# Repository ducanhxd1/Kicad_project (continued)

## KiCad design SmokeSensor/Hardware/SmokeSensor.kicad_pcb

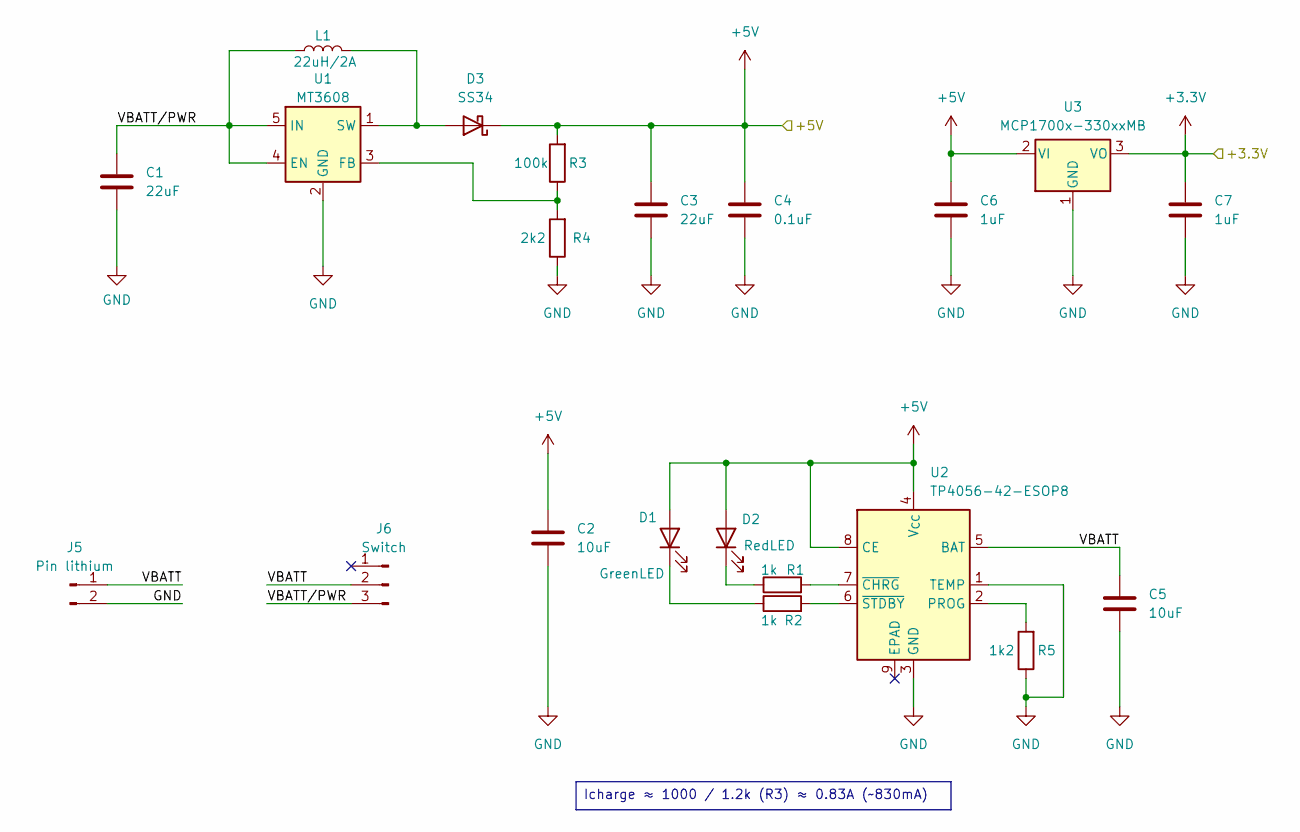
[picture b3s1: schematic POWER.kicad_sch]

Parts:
C1, C3: 22uF; C_0805_2012Metric_Pad1.18x1.45mm_HandSolder
C2, C5: 10uF; C_0805_2012Metric_Pad1.18x1.45mm_HandSolder
C4: 0.1uF; C_0805_2012Metric_Pad1.18x1.45mm_HandSolder
C6, C7: 1uF; C_0805_2012Metric_Pad1.18x1.45mm_HandSolder
D1: GreenLED; LED_0805_2012Metric_Pad1.15x1.40mm_HandSolder
D2: RedLED; LED_0805_2012Metric_Pad1.15x1.40mm_HandSolder
D3: SS34; D_SMA
J5: Pin lithium; JST_PH_S2B-PH-K_1x02_P2.00mm_Horizontal
J6: Switch; PinHeader_1x03_P2.54mm_Vertical
L1: 22uH/2A; L_10.4x10.4_H4.8
R1, R2: 1k; R_0805_2012Metric_Pad1.20x1.40mm_HandSolder
R3: 100k; R_0805_2012Metric_Pad1.20x1.40mm_HandSolder
R4: 2k2; R_0805_2012Metric_Pad1.20x1.40mm_HandSolder
R5: 1k2; R_0805_2012Metric_Pad1.20x1.40mm_HandSolder
U1: MT3608; SOT-23-6
U2: TP4056-42-ESOP8; SOIC-8-1EP_3.9x4.9mm_P1.27mm_EP2.41x3.3mm_ThermalVias
U3: MCP1700x-330xxMB; SOT-89-3

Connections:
+3.3V: C7.1, U3.3 (VO); also elsewhere on the board
+5V: C2.1, C3.1, C4.1, C6.1, D1.2 (A), D2.2 (A), D3.1 (K), R3.2, U2.4 (V_{CC}), U2.8 (CE), U3.2 (VI); also elsewhere on the board
/POWER/VBATT: C5.1, J5.1, J6.2, U2.5 (BAT)
/POWER/VBATT/PWR: C1.1, J6.3, L1.1, U1.4 (EN), U1.5 (IN)
GND: C1.2, C2.2, C3.2, C4.2, C5.2, C6.2, C7.2, J5.2, R4.1, R5.1, U1.2 (GND), U2.1 (TEMP), U2.3 (GND), U3.1 (GND); also elsewhere on the board
unnamed: D1.1 (K), R2.1
unnamed: D2.1 (K), R1.1
unnamed: D3.2 (A), L1.2, U1.1 (SW)
unnamed: R3.1, R4.2, U1.3 (FB)
unnamed: R5.2, U2.2 (PROG)
unnamed: R1.2, U2.7 (~CHRG)
unnamed: R2.2, U2.6 (~STDBY)

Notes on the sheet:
Icharge ≈ 1000 / 1.2k (R3) ≈ 0.83A (~830mA)

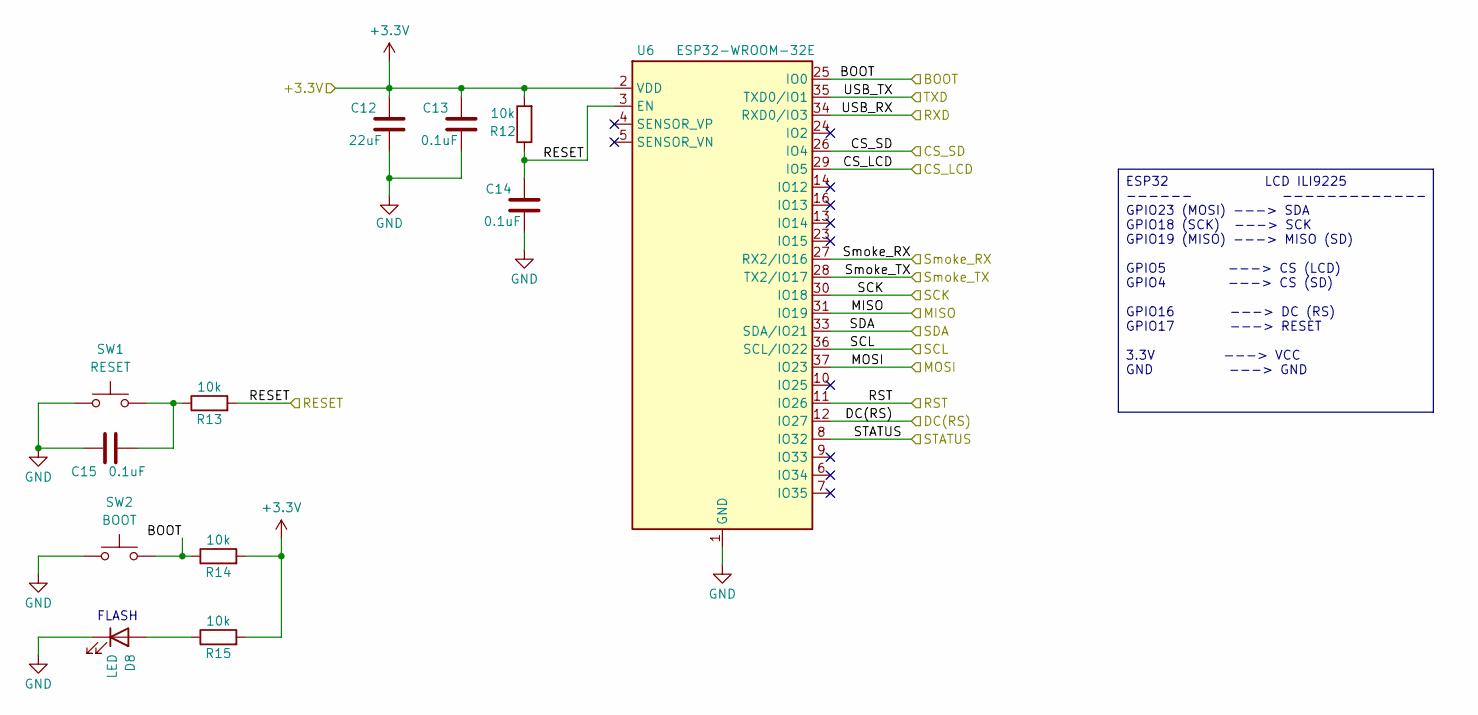
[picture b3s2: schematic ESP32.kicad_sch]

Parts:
C12: 22uF; C_0805_2012Metric_Pad1.18x1.45mm_HandSolder
C13, C14, C15: 0.1uF; C_0805_2012Metric_Pad1.18x1.45mm_HandSolder
D8: LED; LED_0805_2012Metric_Pad1.15x1.40mm_HandSolder
R12, R13, R14, R15: 10k; R_0805_2012Metric_Pad1.20x1.40mm_HandSolder
SW1: RESET; SW_Tactile_SPST_NO_Straight_CK_PTS636Sx25SMTRLFS
SW2: BOOT; SW_Tactile_SPST_NO_Straight_CK_PTS636Sx25SMTRLFS
U6: ESP32-WROOM-32E; ESP32-WROOM-32D

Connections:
+3.3V: C12.1, C13.1, R12.2, R14.2, R15.2, U6.2 (VDD); also elsewhere on the board
/ESP32/BOOT: R14.1, SW2.2, U6.25 (IO0); also elsewhere on the board
/ESP32/CS_LCD: U6.29 (IO5); also elsewhere on the board
/ESP32/CS_SD: U6.26 (IO4); also elsewhere on the board
/ESP32/DC(RS): U6.12 (IO27); also elsewhere on the board
/ESP32/MISO: U6.31 (IO19); also elsewhere on the board
/ESP32/MOSI: U6.37 (IO23); also elsewhere on the board
/ESP32/RESET: C14.1, R12.1, R13.2, U6.3 (EN); also elsewhere on the board
/ESP32/RST: U6.11 (IO26); also elsewhere on the board
/ESP32/SCK: U6.30 (IO18); also elsewhere on the board
/ESP32/SCL: U6.36 (SCL/IO22); also elsewhere on the board
/ESP32/SDA: U6.33 (SDA/IO21); also elsewhere on the board
/ESP32/STATUS: U6.8 (IO32); also elsewhere on the board
/ESP32/Smoke_RX: U6.27 (RX2/IO16); also elsewhere on the board
/ESP32/Smoke_TX: U6.28 (TX2/IO17); also elsewhere on the board
/ESP32/USB_RX: U6.34 (RXD0/IO3); also elsewhere on the board
/ESP32/USB_TX: U6.35 (TXD0/IO1); also elsewhere on the board
GND: C12.2, C13.2, C14.2, C15.1, D8.1 (K), SW1.1, SW2.1, U6.1 (GND), U6.15 (GND), U6.38 (GND), U6.39 (GND); also elsewhere on the board
unnamed: C15.2, R13.1, SW1.2
unnamed: D8.2 (A), R15.1

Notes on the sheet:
FLASH
ESP32 LCD ILI9225 ------ ------------- GPIO23 (MOSI) ---> SDA GPIO18 (SCK) ---> SCK GPIO19 (MISO) ---> MISO (SD) GPIO5 ---> CS (LCD) GPIO4 ---> CS (SD) GPIO16 ---> DC (RS) GPIO17 ---> RESET 3.3V ---> VCC GND ---> GND

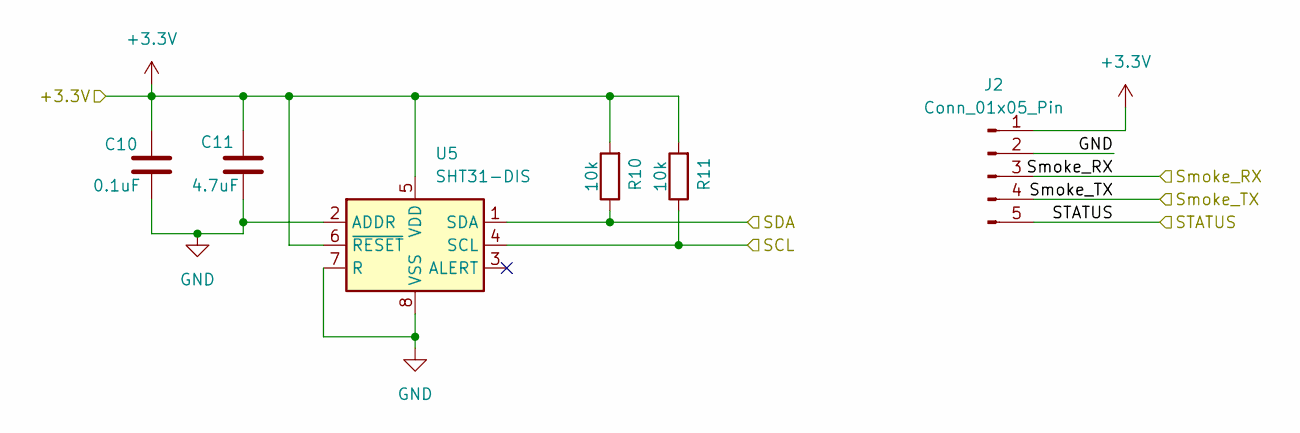
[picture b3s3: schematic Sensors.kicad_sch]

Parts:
C10: 0.1uF; C_0805_2012Metric_Pad1.18x1.45mm_HandSolder
C11: 4.7uF; C_0805_2012Metric_Pad1.18x1.45mm_HandSolder
J2: Conn_01x05_Pin; PinHeader_1x05_P2.54mm_Vertical
R10, R11: 10k; R_0805_2012Metric_Pad1.20x1.40mm_HandSolder
U5: SHT31-DIS; Sensirion_DFN-8-1EP_2.5x2.5mm_P0.5mm_EP1.1x1.7mm

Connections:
+3.3V: C10.1, C11.1, J2.1, R10.2, R11.2, U5.5 (VDD), U5.6 (~RESET); also elsewhere on the board
/ESP32/SCL: R11.1, U5.4 (SCL); also elsewhere on the board
/ESP32/SDA: R10.1, U5.1 (SDA); also elsewhere on the board
/ESP32/STATUS: J2.5; also elsewhere on the board
/ESP32/Smoke_RX: J2.4; also elsewhere on the board
/ESP32/Smoke_TX: J2.3; also elsewhere on the board
GND: C10.2, C11.2, J2.2, U5.2 (ADDR), U5.7 (R), U5.8 (VSS), U5.9 (VSS); also elsewhere on the board

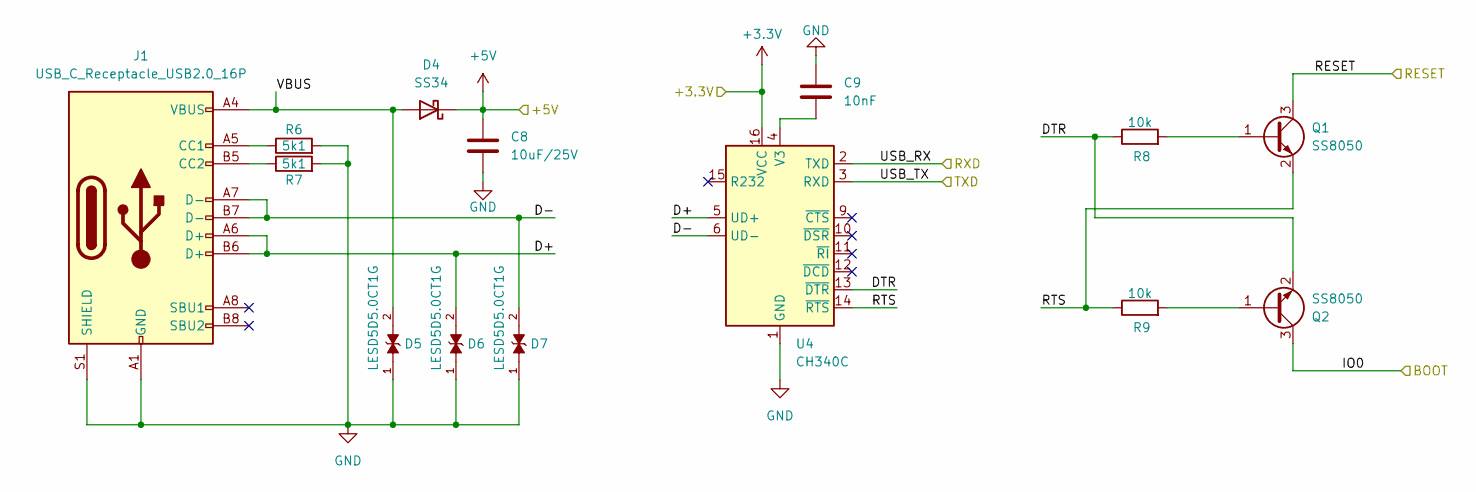
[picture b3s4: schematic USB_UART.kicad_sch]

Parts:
C8: 10uF/25V; C_0805_2012Metric_Pad1.18x1.45mm_HandSolder
C9: 10nF; C_0805_2012Metric_Pad1.18x1.45mm_HandSolder
D4: SS34; D_SMA
D5, D6, D7: LESD5D5.0CT1G; TVS_LESD5D5.0CT1G; PARTREV O
J1: USB_C_Receptacle_USB2.0_16P; USB_C_Receptacle_HCTL_HC-TYPE-C-16P-01A
Q1, Q2: SS8050; SOT-23
R6, R7: 5k1; R_0805_2012Metric_Pad1.20x1.40mm_HandSolder
R8, R9: 10k; R_0805_2012Metric_Pad1.20x1.40mm_HandSolder
U4: CH340C; SOIC-16_3.9x9.9mm_P1.27mm

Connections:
+3.3V: U4.16 (VCC); also elsewhere on the board
+5V: C8.1, D4.1 (K); also elsewhere on the board
/ESP32/BOOT: Q2.3 (C); also elsewhere on the board
/ESP32/RESET: Q1.3 (C); also elsewhere on the board
/ESP32/USB_RX: U4.3 (RXD); also elsewhere on the board
/ESP32/USB_TX: U4.2 (TXD); also elsewhere on the board
/USB UART/D+: D6.2, J1.A6 (D+), J1.B6 (D+), U4.5 (UD+)
/USB UART/D-: D7.2, J1.A7 (D-), J1.B7 (D-), U4.6 (UD-)
/USB UART/DTR: Q2.2 (E), R8.1, U4.13 (~DTR)
/USB UART/RTS: Q1.2 (E), R9.1, U4.14 (~RTS)
/USB UART/VBUS: D4.2 (A), D5.2, J1.A4 (VBUS), J1.A9 (VBUS), J1.B4 (VBUS), J1.B9 (VBUS)
GND: C8.2, C9.1, D5.1, D6.1, D7.1, J1.A1 (GND), J1.A12 (GND), J1.B1 (GND), J1.B12 (GND), J1.S1 (SHIELD), R6.2, R7.2, U4.1 (GND); also elsewhere on the board
unnamed: J1.A5 (CC1), R6.1
unnamed: J1.B5 (CC2), R7.1
unnamed: Q1.1 (B), R8.2
unnamed: Q2.1 (B), R9.2
unnamed: C9.2, U4.4 (V3)

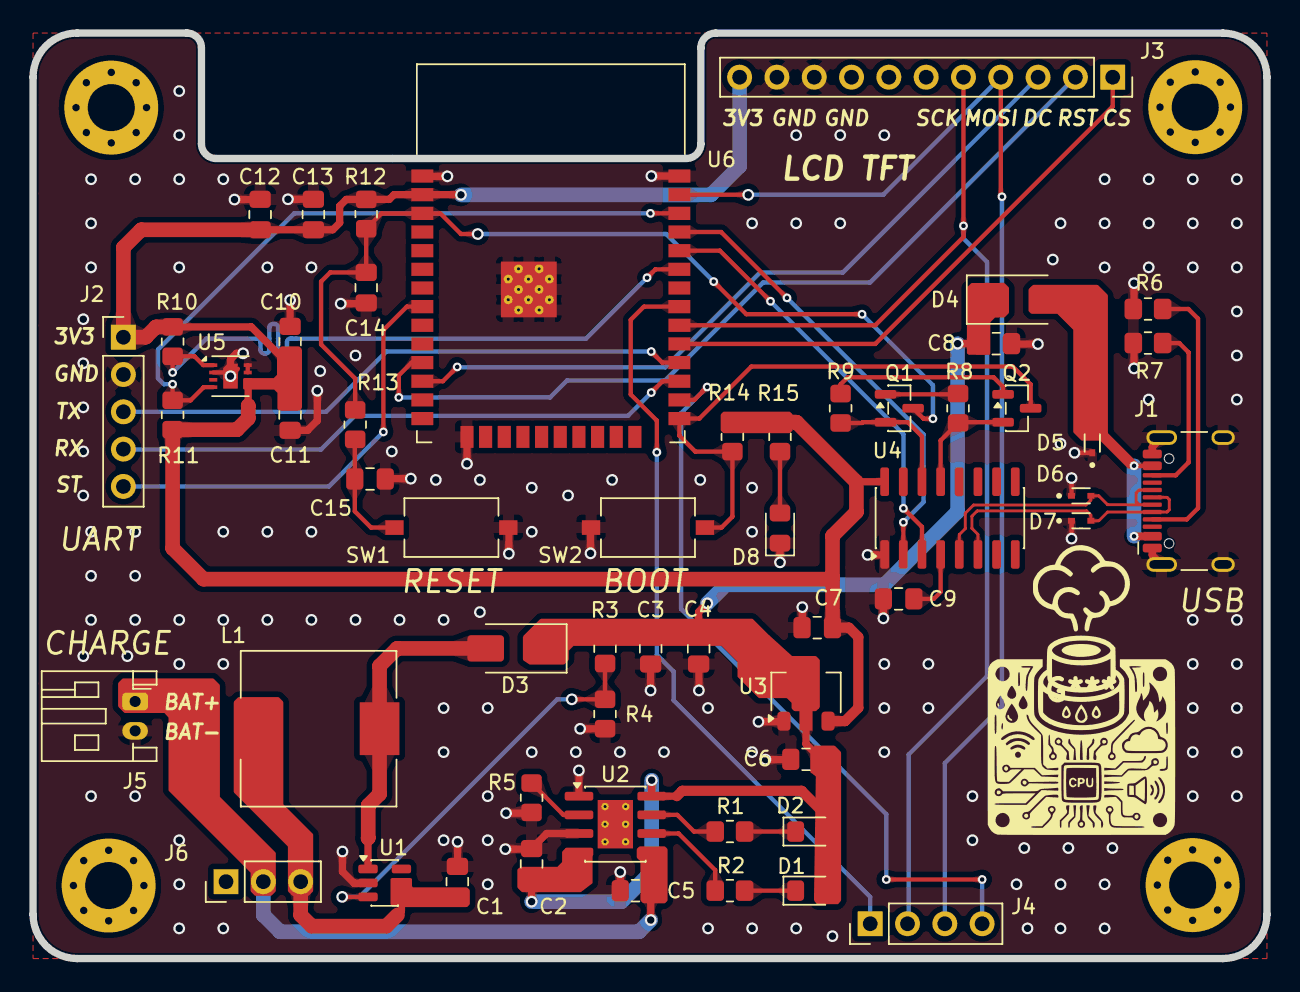
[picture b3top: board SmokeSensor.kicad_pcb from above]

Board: 2 copper layers, 84.0 x 63.0 mm, 55 parts (0 on the bottom side), 40 nets.

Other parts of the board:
J3: Conn_01x11; PinSocket_1x11_P2.54mm_Vertical
J4: Conn_01x04; PinHeader_1x04_P2.54mm_Vertical

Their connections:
+3.3V: J3.11; also elsewhere on the board
/ESP32/CS_LCD: J3.1; also elsewhere on the board
/ESP32/CS_SD: J4.4; also elsewhere on the board
/ESP32/DC(RS): J3.3; also elsewhere on the board
/ESP32/MISO: J4.1; also elsewhere on the board
/ESP32/MOSI: J3.4, J4.3; also elsewhere on the board
/ESP32/RST: J3.2; also elsewhere on the board
/ESP32/SCK: J3.5, J4.2; also elsewhere on the board
GND: J3.9, J3.10; also elsewhere on the board

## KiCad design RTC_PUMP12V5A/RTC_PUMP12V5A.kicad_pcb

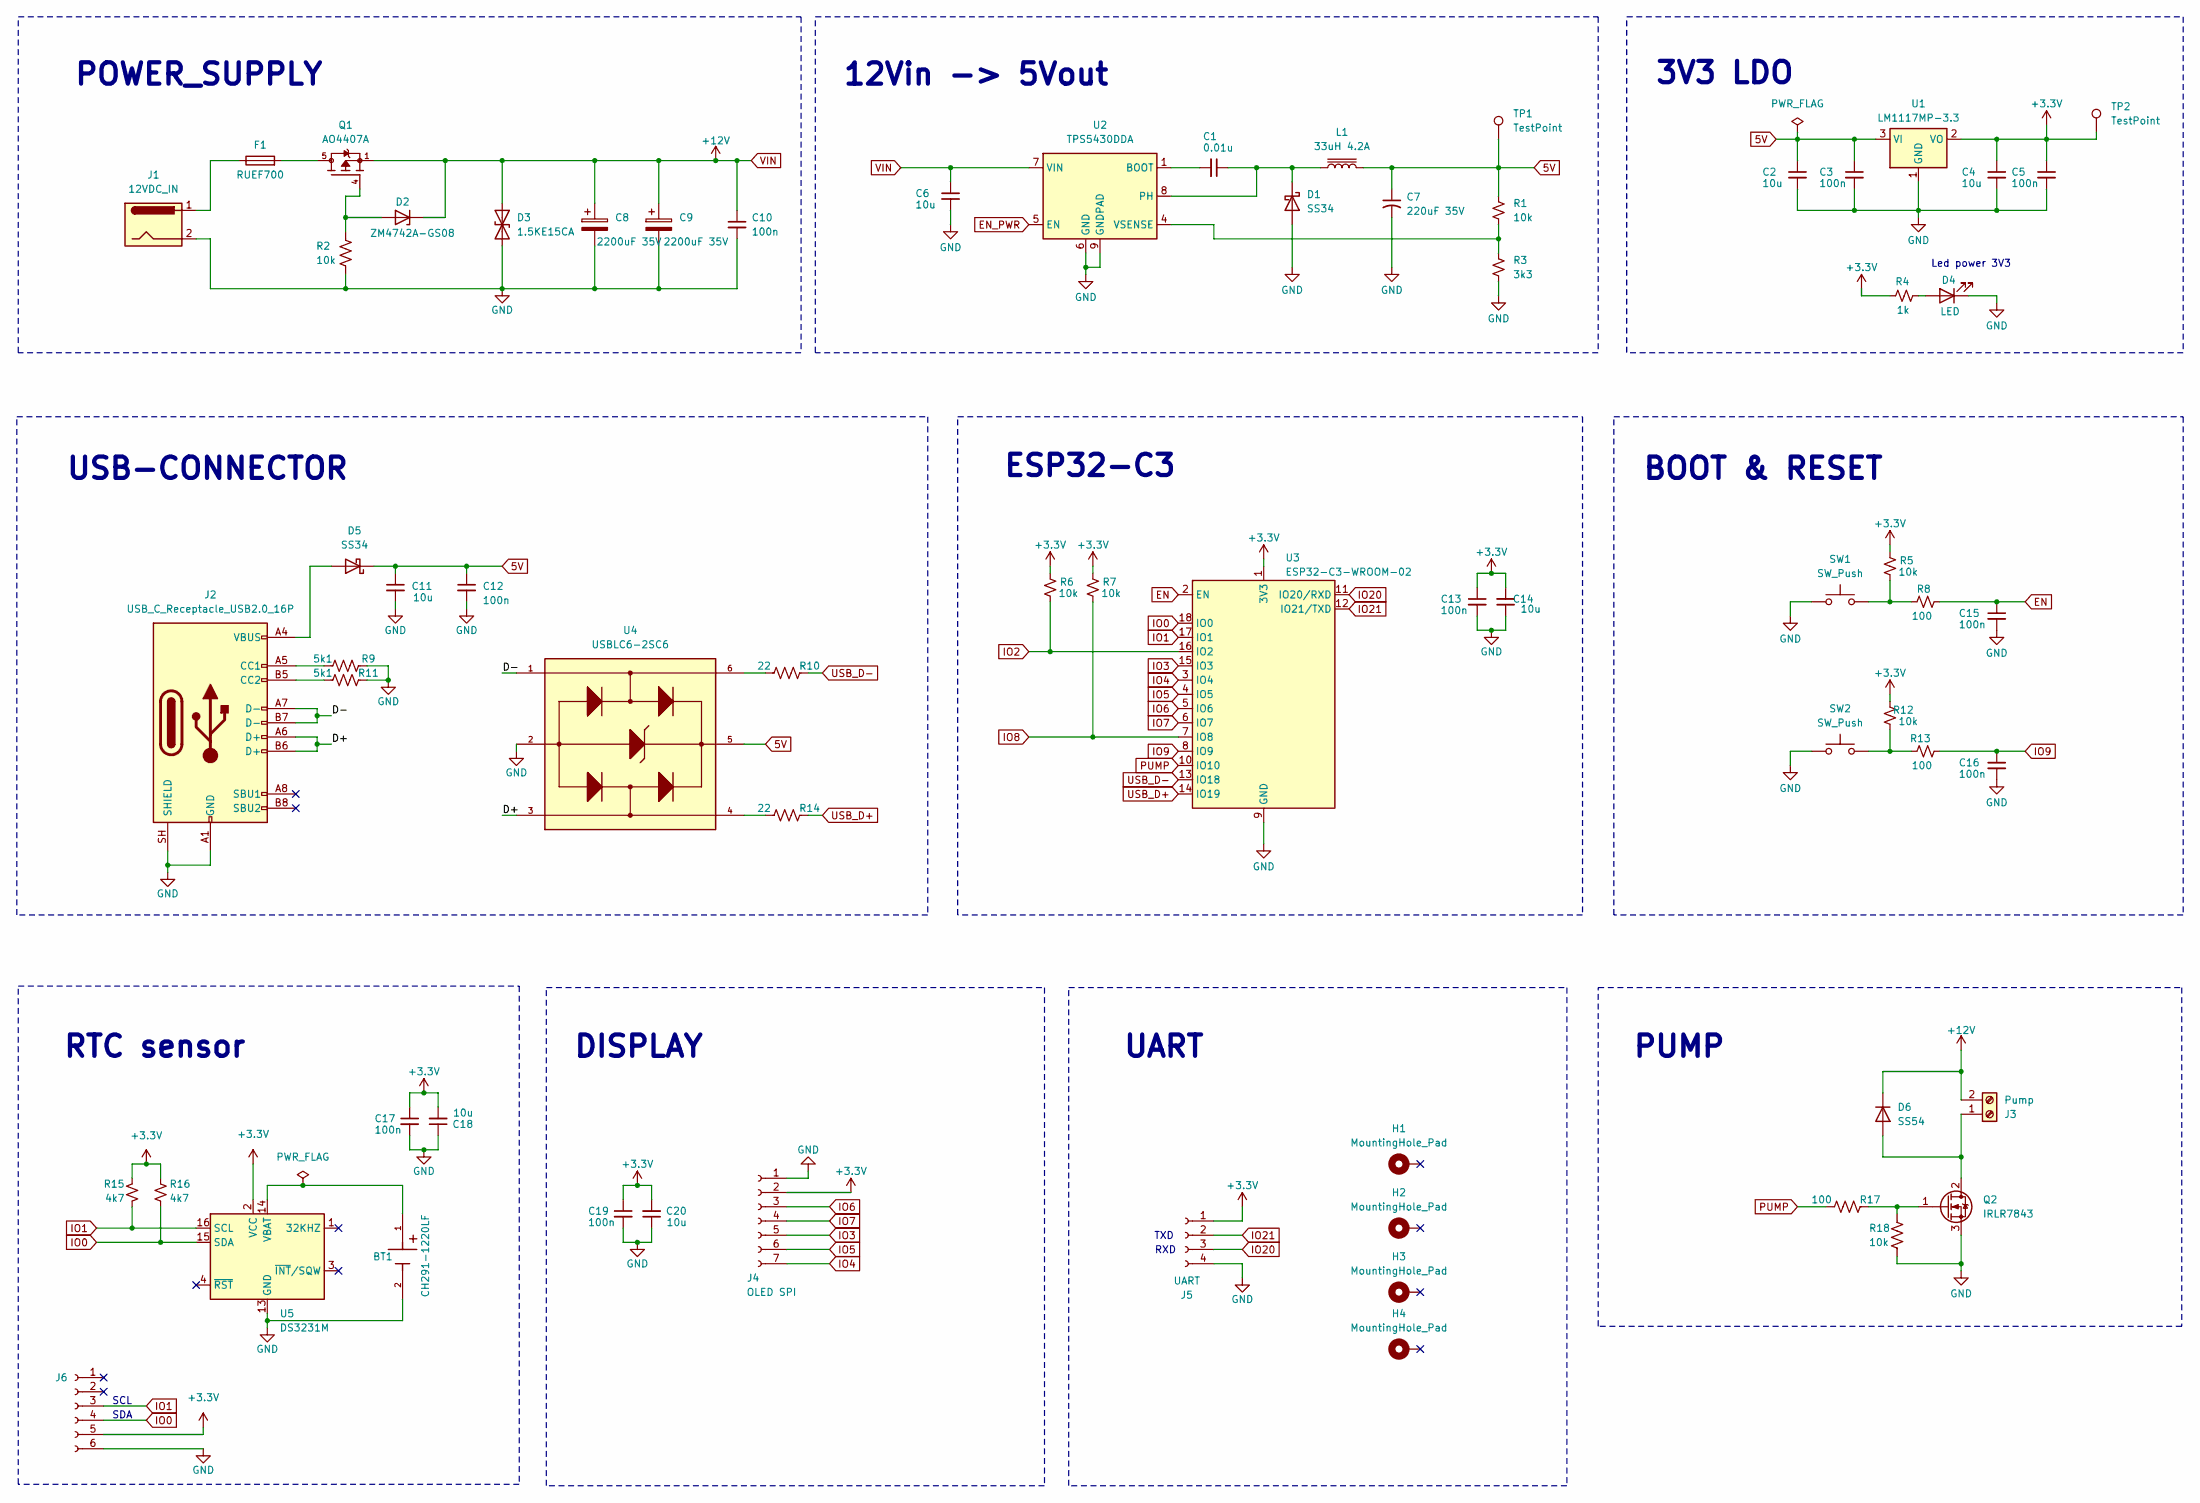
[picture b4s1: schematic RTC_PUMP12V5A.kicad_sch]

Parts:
BT1: CH291-1220LF; Battery_Panasonic_CR2032-HFN_Horizontal_CircularHoles; PARTREV A
C1: 0.01u; C_0805_2012Metric
C2, C4, C6, C11, C14, C18, C20: 10u; C_0805_2012Metric
C3, C5, C10, C12, C13, C15, C16, C17, C19: 100n; C_0805_2012Metric
C7: 220uF 35V; CP_Elec_8x10.5
C8, C9: 2200uF 35V; CP_Radial_D16.0mm_P7.50mm
D1, D5: SS34; D_SMA
D2: ZM4742A-GS08; D_MELF_Handsoldering
D3: 1.5KE15CA; D_DO-201AD_P15.24mm_Horizontal
D4: LED; LED_0805_2012Metric
D6: SS54; ST_D_SMC
F1: RUEF700; FUSRR505W81L660T250H1360
H1, H2, H3, H4: MountingHole_Pad; MountingHole_3.5mm_Pad
J1: 12VDC_IN; BarrelJack_Horizontal
J2: USB_C_Receptacle_USB2.0_16P; USB_C_Receptacle_HRO_TYPE-C-31-M-12
J3: Pump; PhoenixContact_MC_1,5_2-G-3.81_1x02_P3.81mm_Horizontal
J4: OLED SPI; PinSocket_1x07_P2.54mm_Vertical
J5: UART; JST_XH_B4B-XH-A_1x04_P2.50mm_Vertical
J6: Conn_01x06_Socket; PinSocket_1x06_P2.54mm_Vertical
L1: 33uH 4.2A; L_Bourns_SRR1208_12.7x12.7mm
Q1: AO4407A; SOIC127P600X175-8N; PARTREV I
Q2: IRLR7843; TO-252-2
R1, R2, R5, R6, R7, R12, R18: 10k; R_0805_2012Metric
R3: 3k3; R_0805_2012Metric
R4: 1k; R_0805_2012Metric
R8, R13, R17: 100; R_0805_2012Metric
R9, R11: 5k1; R_0805_2012Metric
R10, R14: 22; R_0805_2012Metric
R15, R16: 4k7; R_0805_2012Metric
SW1, SW2: SW_Push; SW_Tactile_SPST_NO_Straight_CK_PTS636Sx25SMTRLFS
TP1, TP2: TestPoint; Pin_D1.0mm_L10.0mm
U1: LM1117MP-3.3; SOT-223-3_TabPin2
U2: TPS5430DDA; TI_SO-PowerPAD-8_ThermalVias
U3: ESP32-C3-WROOM-02
U4: USBLC6-2SC6; SOT95P280X145-6N
U5: DS3231M; SOIC-16W_7.5x10.3mm_P1.27mm

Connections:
5V: C2.1, C3.1, C7.1, C11.1, C12.1, D5.1 (K), L1.2, R1.1, TP1.1 (1_1), U1.3 (VI), U4.5
+3.3V: C4.1, C5.1, C13.1, C14.2, C17.1, C18.2, C19.1, C20.2, J4.2, J5.1, J6.5, R4.1, R5.2, R6.2, R7.2, R12.2, R15.2, R16.2, TP2.1 (1_1), U1.2 (VO), U3.1 (3V3), U5.2 (VCC)
/D+: J2.A6 (D+), J2.B6 (D+), U4.3
/D-: J2.A7 (D-), J2.B7 (D-), U4.1
EN: C15.1, R8.2, U3.2 (EN)
EN_PWR: U2.5 (EN)
GND: BT1.2, C2.2, C3.2, C4.2, C5.2, C6.2, C7.2, C8.2, C9.2, C10.2, C11.2, C12.2, C13.2, C14.1, C15.2, C16.2, C17.2, C18.1, C19.2, C20.1, D1.2 (A), D3.2 (A2), D4.1 (K), J1.2, J1.3, J2.A1 (GND), J2.A12 (GND), J2.B1 (GND), J2.B12 (GND), J2.SH (SHIELD), J4.1, J5.4, J6.6, Q2.3 (S), R2.2, R3.2, R9.2, R11.2, R18.1, SW1.1, SW2.1, U1.1 (GND), U2.6 (GND), U2.9 (GNDPAD), U3.9 (GND), U3.19 (GND), U4.2, U5.5 (GND), U5.6 (GND), U5.7 (GND), U5.8 (GND), U5.9 (GND), U5.10 (GND), U5.11 (GND), U5.12 (GND), U5.13 (GND)
IO0: J6.4, R16.1, U3.18 (IO0), U5.15 (SDA)
IO1: J6.3, R15.1, U3.17 (IO1), U5.16 (SCL)
IO2: R6.1, U3.16 (IO2)
IO3: J4.5, U3.15 (IO3)
IO4: J4.7, U3.3 (IO4)
IO5: J4.6, U3.4 (IO5)
IO6: J4.3, U3.5 (IO6)
IO7: J4.4, U3.6 (IO7)
IO8: R7.1, U3.7 (IO8)
IO9: C16.1, R13.2, U3.8 (IO9)
IO20: J5.3, U3.11 (IO20/RXD)
IO21: J5.2, U3.12 (IO21/TXD)
unnamed: C1.1, D1.1 (K), L1.1, U2.8 (PH)
unnamed: D2.2 (A), Q1.4, R2.1
unnamed: D4.2 (A), R4.2
unnamed: D5.2 (A), J2.A4 (VBUS), J2.A9 (VBUS), J2.B4 (VBUS), J2.B9 (VBUS)
unnamed: D6.2 (A), J3.1, Q2.2 (D)
unnamed: F1.1, J1.1
unnamed: F1.2, Q1.5, Q1.6, Q1.7, Q1.8
unnamed: J2.A5 (CC1), R9.1
unnamed: J2.B5 (CC2), R11.1
unnamed: Q2.1 (G), R17.2, R18.2
unnamed: R5.1, R8.1, SW1.2
unnamed: R10.1, U4.6
unnamed: R12.1, R13.1, SW2.2
unnamed: R14.1, U4.4
unnamed: C1.2, U2.1 (BOOT)
unnamed: R1.2, R3.1, U2.4 (VSENSE)
unnamed: BT1.1, U5.14 (VBAT)
PUMP: R17.1, U3.10 (IO10)
USB_D+: R14.2, U3.14 (IO19)
USB_D-: R10.2, U3.13 (IO18)
VIN: C6.1, C8.1, C9.1, C10.1, D2.1 (K), D3.1 (A1), D6.1 (K), J3.2, Q1.1, Q1.2, Q1.3, U2.7 (VIN)

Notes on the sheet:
3V3 LDO
PUMP
RXD
Led power 3V3
USB-CONNECTOR
SCL
SDA
ESP32-C3
RTC sensor
DISPLAY
TXD
12Vin -> 5Vout
POWER_SUPPLY
BOOT & RESET
UART

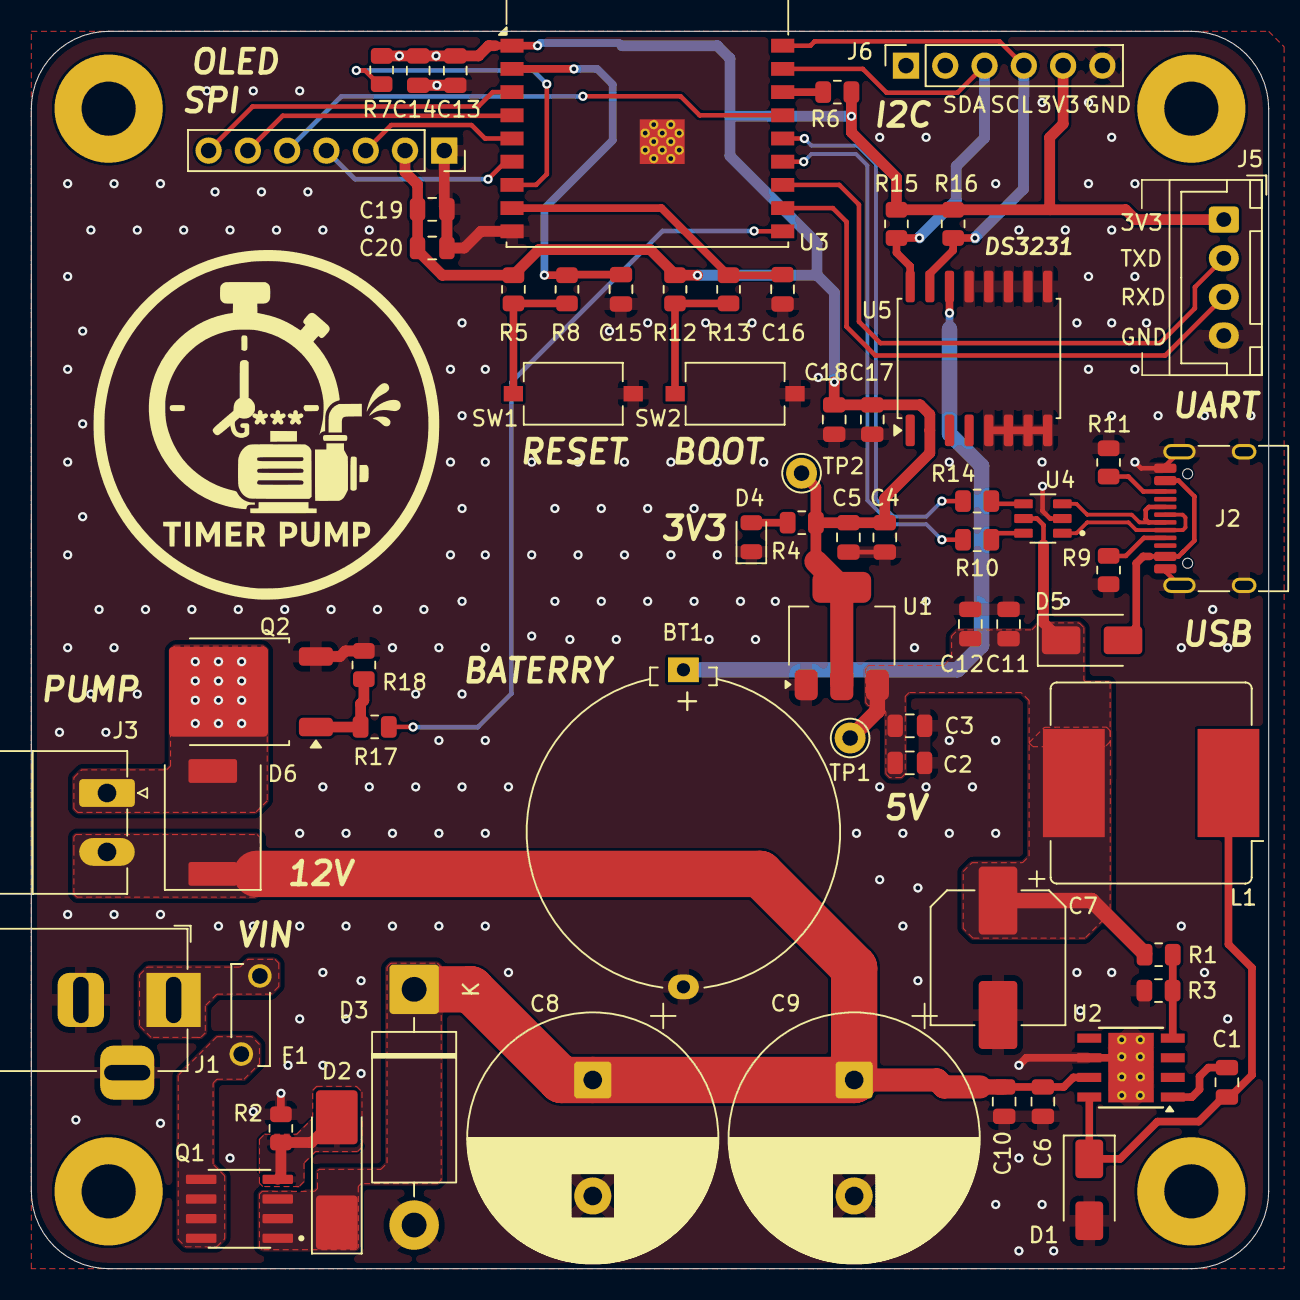
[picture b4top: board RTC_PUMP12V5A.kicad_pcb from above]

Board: 2 copper layers, 80.0 x 80.0 mm, 68 parts (0 on the bottom side), 39 nets.

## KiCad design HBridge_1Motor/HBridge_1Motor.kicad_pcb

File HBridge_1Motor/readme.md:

# HBridge_1Motor

Bo mạch điều khiển động cơ sử dụng cầu H, được thiết kế bằng KiCad. Thư mục dự án gồm sơ đồ nguyên lý, PCB và hình ảnh mô hình 3D để tham khảo khi đọc thiết kế và lắp ráp.

> **Lưu ý:** Các thông số như điện áp làm việc, dòng tối đa, tần số PWM và giới hạn nhiệt chưa được ghi rõ trong tài liệu hiện có. Hãy kiểm tra sơ đồ, datasheet và tính toán nhiệt trước khi cấp nguồn hoặc kết nối động cơ.

## Hình ảnh PCB

**Mặt trên**

**Mặt dưới**

Kích thước board hiển thị trong mô hình 3D xấp xỉ 72 x 73 mm.

## Tổng quan thiết kế

Mạch gồm các khối chính sau:

| Khối | Thành phần / chức năng |
| --- | --- |
| Công suất động cơ | MOSFET IRF3205, driver gate IR2104 và điện trở shunt R28 (0.02 ohm, 5 W). |
| Nguồn | Đầu vào được đánh dấu VIN+ / VIN-; mạch có các đường nguồn +12 V, +5 V và +3.3 V. Sơ đồ sử dụng XL4015 và AMS1117-5.0. |
| Điều khiển | PCB có các nhãn DIR và PUL; schematic có các net PWM, DIR, IN_L, IN_R và DIR_MCU. Hãy đối chiếu sơ đồ để xác nhận ánh xạ chân trước khi kết nối bộ điều khiển. |
| Cách ly tín hiệu | Schematic có các linh kiện 6N137 và PC817. |
| Cảm biến và xử lý tín hiệu | Các cảm biến quang GP1S093HCZ0F, cùng LM393 và MCP6002. |
| Bảo vệ / hiển thị | Schematic có TVS SMAJ28A, các diode và LED. |

Bảng trên tóm tắt các linh kiện nhận diện được từ schematic, không thay thế cho việc truy mạch và kiểm tra datasheet.

## Đầu nối trên PCB

| Nhãn trên PCB | Ý nghĩa theo silkscreen |
| --- | --- |
| VIN+ / VIN- | Đầu vào nguồn. |
| GND / DIR / PUL / 3V3 | Header tín hiệu điều khiển và mass. Đối chiếu schematic để xác nhận từng chân. |
| GND / MT1 / MT2 | Đầu nối tải theo nhãn trên PCB. |

Hãy đối chiếu hướng chân và net trong schematic trước khi đấu dây; không suy diễn cực tính hoặc chức năng chân chỉ từ vị trí đầu nối.

## Cấu trúc thư mục

```text
HBridge_1Motor/
|-- 01Docs/
|   |-- IMG/                 # Hình mô hình 3D PCB
|   `-- LIB/                 # Thư viện 3D, footprint và symbol
|-- 02Schematic/
|   `-- schematic.pdf        # Sơ đồ nguyên lý xuất PDF
|-- 03PCBLayout/
|   |-- HBridge_1Motor.kicad_pro
|   |-- HBridge_1Motor.kicad_sch
|   |-- HBridge_1Motor.kicad_pcb
|   `-- fp-lib-table
|-- 04Manufacturing/
|   |-- bom/ibom.html        # BOM tương tác
|   `-- gerber_to_order/     # Gói Gerber/Excellon theo nhà sản xuất
`-- readme.md
```

- [Sơ đồ nguyên lý dạng PDF](02Schematic/schematic.pdf) — tiện xem nhanh hoặc chia sẻ mà không cần mở KiCad.
- [BOM tương tác](04Manufacturing/bom/ibom.html) — mở bằng trình duyệt để tra cứu linh kiện trên PCB.

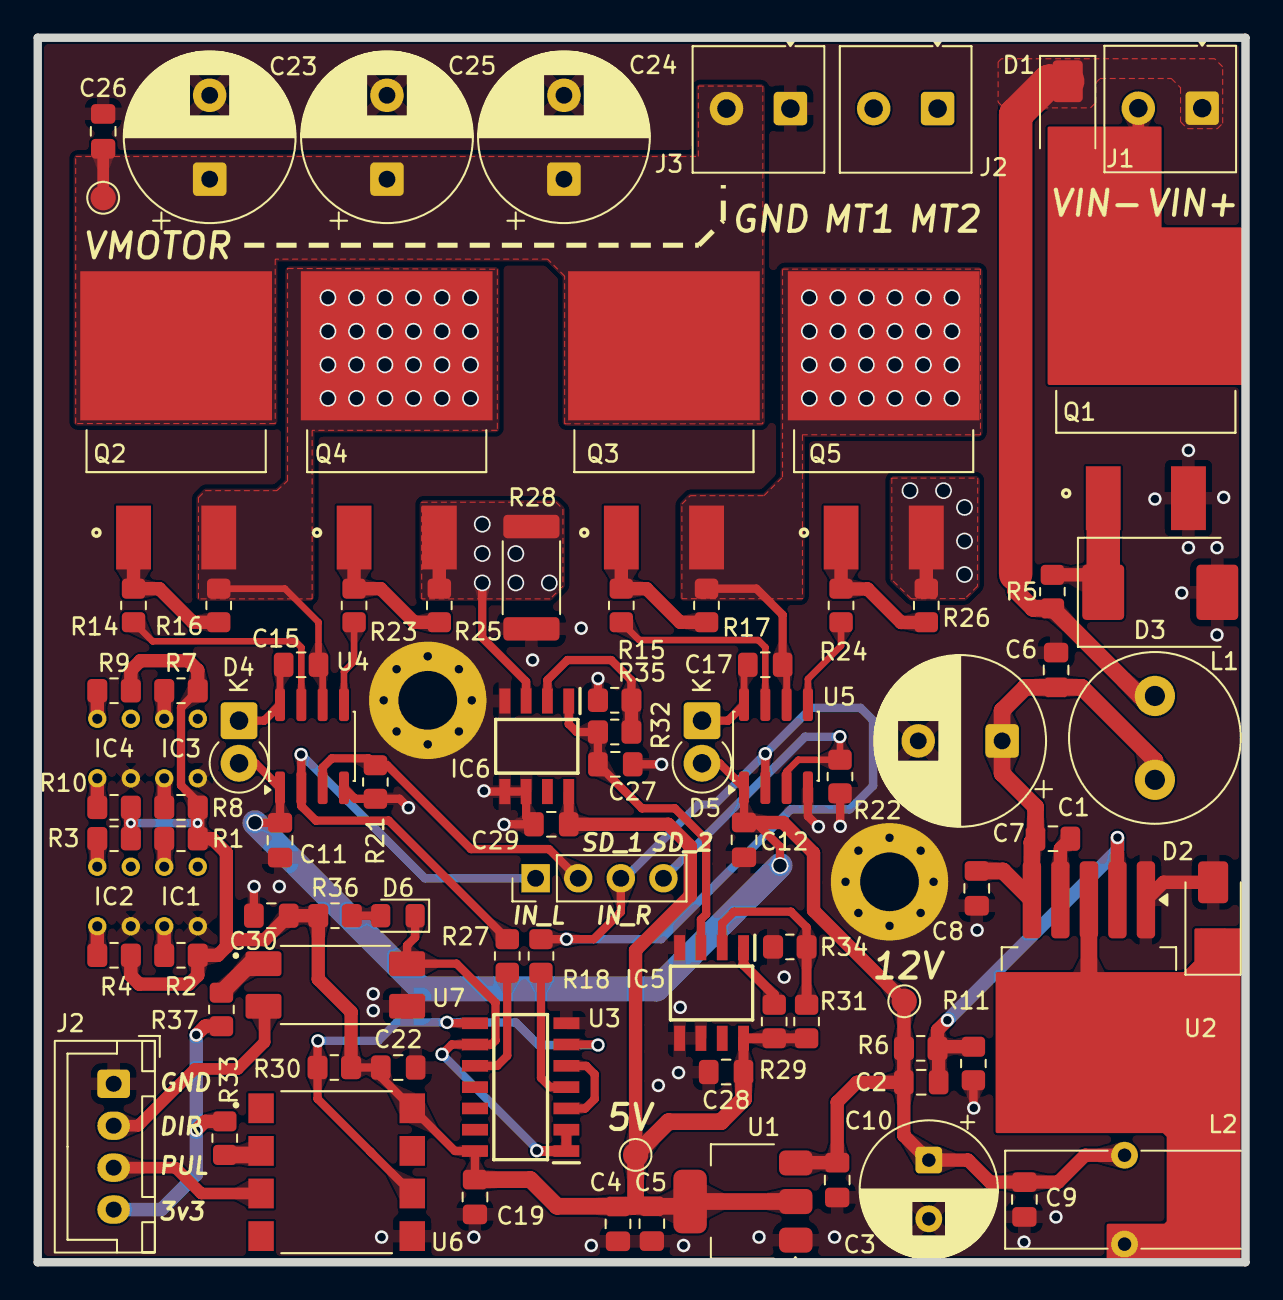
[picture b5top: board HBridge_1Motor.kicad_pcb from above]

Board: 2 copper layers, 72.0 x 73.0 mm, 90 parts (0 on the bottom side), 51 nets.

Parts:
C1, C8, C9, C15, C17: 105; C_0805_2012Metric_Pad1.18x1.45mm_HandSolder
C2: 33n; C_0805_2012Metric_Pad1.18x1.45mm_HandSolder
C3: 22u; C_0805_2012Metric_Pad1.18x1.45mm_HandSolder
C4: 10u; C_0805_2012Metric_Pad1.18x1.45mm_HandSolder
C5, C6, C11, C12, C19, C22, C28, C29, C30: 104; C_0805_2012Metric_Pad1.18x1.45mm_HandSolder
C7: 220uF/50V; CP_Radial_D10.0mm_P5.00mm
C10: 330uF/25V; CP_Radial_D8.0mm_P3.50mm
C23, C24, C25: 470uF/50V; CP_Radial_D10.0mm_P5.00mm
C26: 104/50V; C_0805_2012Metric_Pad1.18x1.45mm_HandSolder
C27: 10n; C_0805_2012Metric_Pad1.18x1.45mm_HandSolder
D1: SMAJ28A; D_SMA
D2: SS54F; D_SMA
D3: ZZM12; D_SMC
D4, D5: UF4007; D_DO-41_SOD81_P2.54mm_Vertical_CathodeUp
D6: LED; LED_0805_2012Metric_Pad1.15x1.40mm_HandSolder
IC1, IC2, IC3, IC4: GP1S093HCZ0F
IC5: LM393DR; SOIC127P600X175-8N
IC6: MCP6002-I_SN; SOIC127P600X175-8N
J1: +24V_Vin; TerminalBlock_Phoenix_MKDS-1-2-3.81_1x02_P3.81mm_Horizontal
J2: MOTOR; TerminalBlock_Phoenix_MKDS-1-2-3.81_1x02_P3.81mm_Horizontal
J2#2: Conn_01x04_Pin; JST_XH_B4B-XH-A_1x04_P2.50mm_Vertical
J3: V_Motor; TerminalBlock_Phoenix_MKDS-1-2-3.81_1x02_P3.81mm_Horizontal
L1: 4.7uH 5A; L_Radial_D10.0mm_P5.00mm_Neosid_SD12k_style3
L2: 47uH/5A; L_Toroid_Vertical_L14.0mm_W5.6mm_P5.30mm_Bourns_5700
Q1, Q2, Q3, Q4, Q5: IRF3205SPBF; TRANS_IRF3205SPBF
R1, R3, R5, R7, R9, R16, R17, R21, R22, R25, R26: 10K; R_0805_2012Metric_Pad1.20x1.40mm_HandSolder
R2, R4, R8, R10, R33, R37: 220; R_0805_2012Metric_Pad1.20x1.40mm_HandSolder
R6: 13K; R_0805_2012Metric_Pad1.20x1.40mm_HandSolder
R11: 1.5K; R_0805_2012Metric_Pad1.20x1.40mm_HandSolder
R14, R15, R23, R24: 22; R_0805_2012Metric_Pad1.20x1.40mm_HandSolder
R18, R27, R29: 4K7; R_0805_2012Metric_Pad1.20x1.40mm_HandSolder
R28: 0.02 (5W); R_2512_6332Metric_Pad1.40x3.35mm_HandSolder
R30: 3K3; R_0805_2012Metric_Pad1.20x1.40mm_HandSolder
R31: 2K; R_0805_2012Metric_Pad1.20x1.40mm_HandSolder
R32: 14K; R_0805_2012Metric_Pad1.20x1.40mm_HandSolder
R34: 3K; R_0805_2012Metric_Pad1.20x1.40mm_HandSolder
R35, R36: 1K; R_0805_2012Metric_Pad1.20x1.40mm_HandSolder
TP1: 12V; TestPoint_Pad_D1.5mm
TP2: 5V; TestPoint_Pad_D1.5mm
TP3: V_MOTOR; TestPoint_Pad_D1.5mm
U1: AMS1117-5.0; SOT-223-3_TabPin2
U2: XL4015; TO-263-5_TabPin3
U3: 4001; SOIC127P600X175-14N
U4, U5: IR2104; SOIC-8_3.9x4.9mm_P1.27mm
U6: 6N137; COUPL_6N138SDM
U7: PC817; SOIC254P960X420-4N

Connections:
3v3_MCU: J2#2.4, R33.1, R37.1
+5V: C4.1, C5.1, C19.1, C22.1, C28.1, C29.1, C30.1, IC5.8 (VCC), IC6.8 (VDD), R1.2, R2.2, R3.2, R4.2, R7.2, R8.2, R9.2, R10.2, R29.1, R30.2, R31.1, R36.2, TP2.1 (1_1), U1.2 (VO), U3.14 (VDD), U6.8 (VCC)
+12V: C2.1, C3.1, C9.1, C10.1, C11.1, C12.1, D4.2 (A), D5.2 (A), L2.2, R6.2, TP1.1 (1_1), U1.3 (VI), U4.1 (VCC), U5.1 (VCC)
+V_MOTOR: C23.1, C24.1, C25.1, C26.1, J3.2, Q2.2, Q3.2, TP3.1 (1_1)
DIR: D6.1 (K), U3.1, U3.2, U3.9, U7.4
DIR_MCU: J2#2.2, U7.2
FAULT: IC5.1 (1OUT), R29.2
GH_1: R14.1, U4.7 (HO)
GH_2: R15.1, U5.7 (HO)
GL_1: R23.1, U4.5 (LO)
GL_2: R24.1, U5.5 (LO)
GND: C3.2, C4.2, C5.2, C6.2, C7.2, C8.2, C9.2, C10.2, C11.2, C12.2, C19.2, C22.2, C23.2, C24.2, C25.2, C26.2, C27.2, C28.2, C29.2, C30.2, D2.2 (A), D3.2 (A), IC1.4 (CATHODE), IC2.4 (CATHODE), IC3.4 (CATHODE), IC4.4 (CATHODE), IC5.4 (GND), IC5.5 (2IN+), IC5.6 (2IN-), IC6.4 (VSS), IC6.5 (VINB+), IC6.6 (VINB-), J2#2.1, J3.1, Q1.3, R11.1, R21.1, R22.1, R28.2, R34.2, R35.2, U1.1 (GND), U2.1 (GND), U3.7 (VSS), U4.4 (COM), U5.4 (COM), U6.5 (GND), U7.3
IN_L: R27.2, U4.2 (IN)
IN_R: R18.2, U5.2 (IN)
MCU_ADC: C27.1, IC5.3 (1IN+), IC6.1 (VOUTA), R32.1
MOTOR1: C15.2, J2.2, Q2.3, Q4.2, R16.1, U4.6 (VS)
MOTOR2: C17.2, J2.1, Q3.3, Q5.2, R17.1, U5.6 (VS)
unnamed: D1.1 (A1), J1.1, L1.1, R5.1
unnamed: D1.2 (A2), J1.2, Q1.2
unnamed: D2.1 (K), L2.1, U2.3 (SW)
unnamed: D3.1 (K), Q1.1, R5.2
unnamed: C15.1, D4.1 (K), U4.8 (VB)
unnamed: C17.1, D5.1 (K), U5.8 (VB)
unnamed: D6.2 (A), R36.1
unnamed: IC1.1 (ANODE), R2.1
unnamed: IC1.2 (COLLECTOR), R1.1
unnamed: IC2.1 (ANODE), R4.1
unnamed: IC2.2 (COLLECTOR), R3.1
unnamed: IC3.1 (ANODE), R8.1
unnamed: IC3.2 (COLLECTOR), R7.1
unnamed: IC4.1 (ANODE), R10.1
unnamed: IC4.2 (COLLECTOR), R9.1
unnamed: IC5.2 (1IN-), R31.2, R34.1
unnamed: IC6.2 (VINA-), R32.2, R35.1
unnamed: Q2.1, R14.2, R16.2
unnamed: Q3.1, R15.2, R17.2
unnamed: Q4.1, R23.2, R25.2
unnamed: Q5.1, R24.2, R26.2
unnamed: R18.1, U3.4
unnamed: R27.1, U3.10
unnamed: R37.2, U7.1
unnamed: C2.2, R6.1, R11.2, U2.2 (FB)
unnamed: C1.2, U2.4 (VC)
unnamed: C1.1, C6.1, C7.1, C8.1, L1.2, U2.5 (VIN)
unnamed: U3.3, U3.5
unnamed: R33.2, U6.2 (A)
PULSE_MCU: J2#2.3, U6.3 (C)
PWM: R30.1, U3.6, U3.8, U6.6 (VO)
Rshunt: IC6.3 (VINA+), Q4.3, Q5.3, R25.1, R26.1, R28.1
SD_1: R21.2, U4.3 (~SD)
SD_2: R22.2, U5.3 (~SD)
